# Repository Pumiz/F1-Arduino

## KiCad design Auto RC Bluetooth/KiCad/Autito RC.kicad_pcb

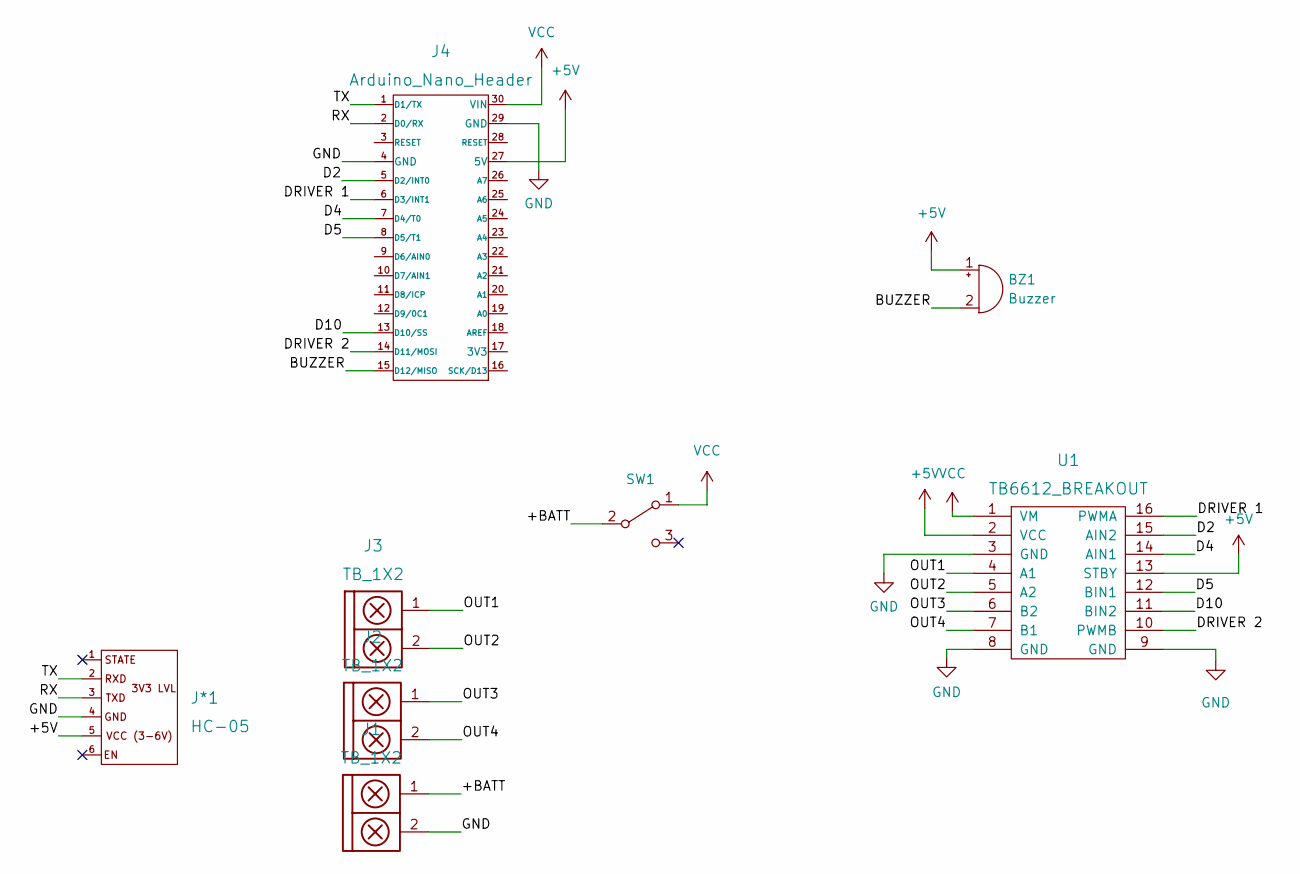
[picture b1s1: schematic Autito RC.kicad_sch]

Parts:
BZ1: Buzzer; Buzzer_12mm
J1, J2, J3: TB_1X2; BORNERA2_AZUL
J4: Arduino_Nano_Header; arduino_nano_header
J*1: HC-05
SW1: SW_SPDT; SW_SPDT_TH_Vertical
U1: TB6612_BREAKOUT; TB6612_Breakout

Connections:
+5V: BZ1.1 (-), J4.27 (5V), J*1.5, U1.2 (VCC), U1.13 (STBY)
/+BATT: J1.1, SW1.2 (B)
/BUZZER: BZ1.2 (+), J4.15 (D12/MISO)
/D2: J4.5 (D2/INT0), U1.15 (AIN2)
/D4: J4.7 (D4/T0), U1.14 (AIN1)
/D5: J4.8 (D5/T1), U1.12 (BIN1)
/D10: J4.13 (D10/SS), U1.11 (BIN2)
/DRIVER 1: J4.6 (D3/INT1), U1.16 (PWMA)
/DRIVER 2: J4.14 (D11/MOSI), U1.10 (PWMB)
/OUT1: J3.1, U1.4 (A1)
/OUT2: J3.2, U1.5 (A2)
/OUT3: J2.1, U1.6 (B2)
/OUT4: J2.2, U1.7 (B1)
/RX: J4.2 (D0/RX), J*1.3
/TX: J4.1 (D1/TX), J*1.2
GND: J1.2, J4.4 (GND), J4.29 (GND), J*1.4, U1.3 (GND), U1.8 (GND), U1.9 (GND)
VCC: J4.30 (VIN), SW1.1 (A), U1.1 (VM)

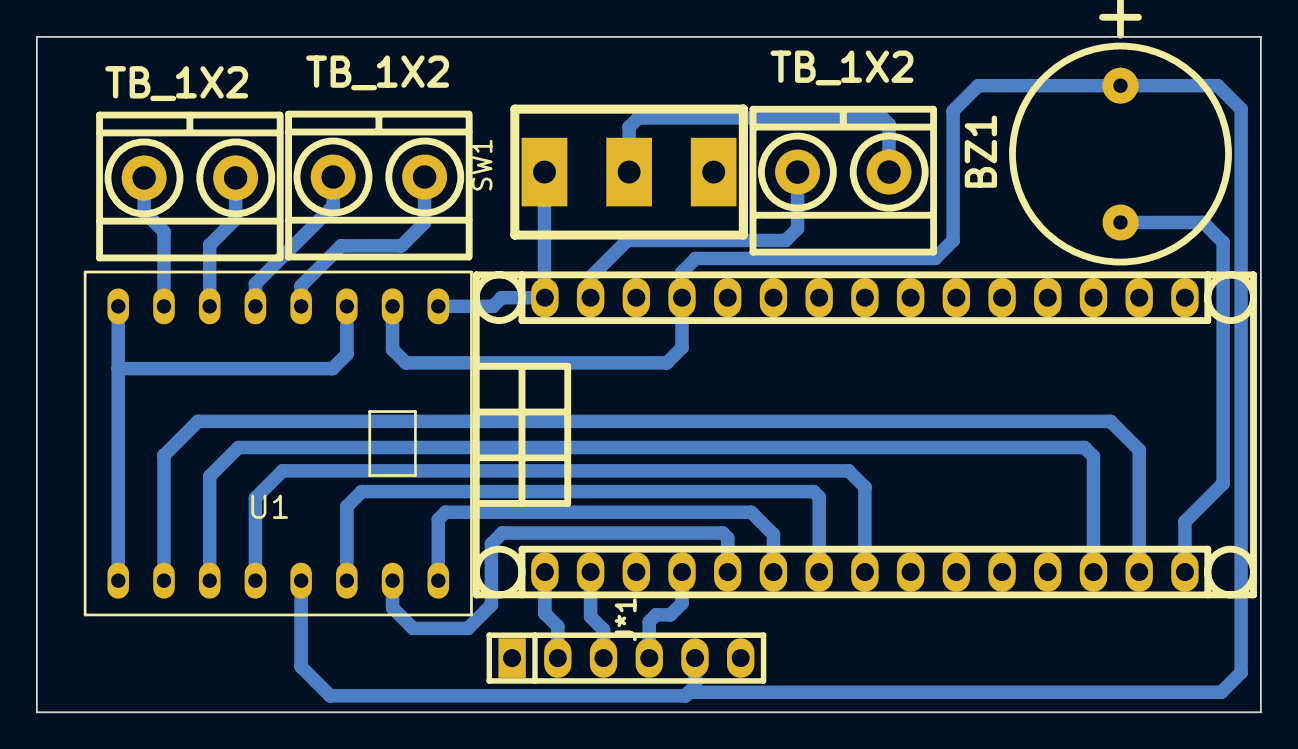
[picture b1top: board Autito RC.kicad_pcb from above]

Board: 2 copper layers, 68.0 x 37.5 mm, 8 parts (0 on the bottom side), 17 nets.

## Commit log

2022-09-29 Agregue el codigo de F1 y la carpeta del autoBluetooth
2022-10-27 Agregue el diseño del PCB
2023-09-06 STL´S del chasis 1/10
